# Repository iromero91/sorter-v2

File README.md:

# Sorter V2
## A LEGO® Sorting Machine

[More details](https://basically.website/sorter-v2)

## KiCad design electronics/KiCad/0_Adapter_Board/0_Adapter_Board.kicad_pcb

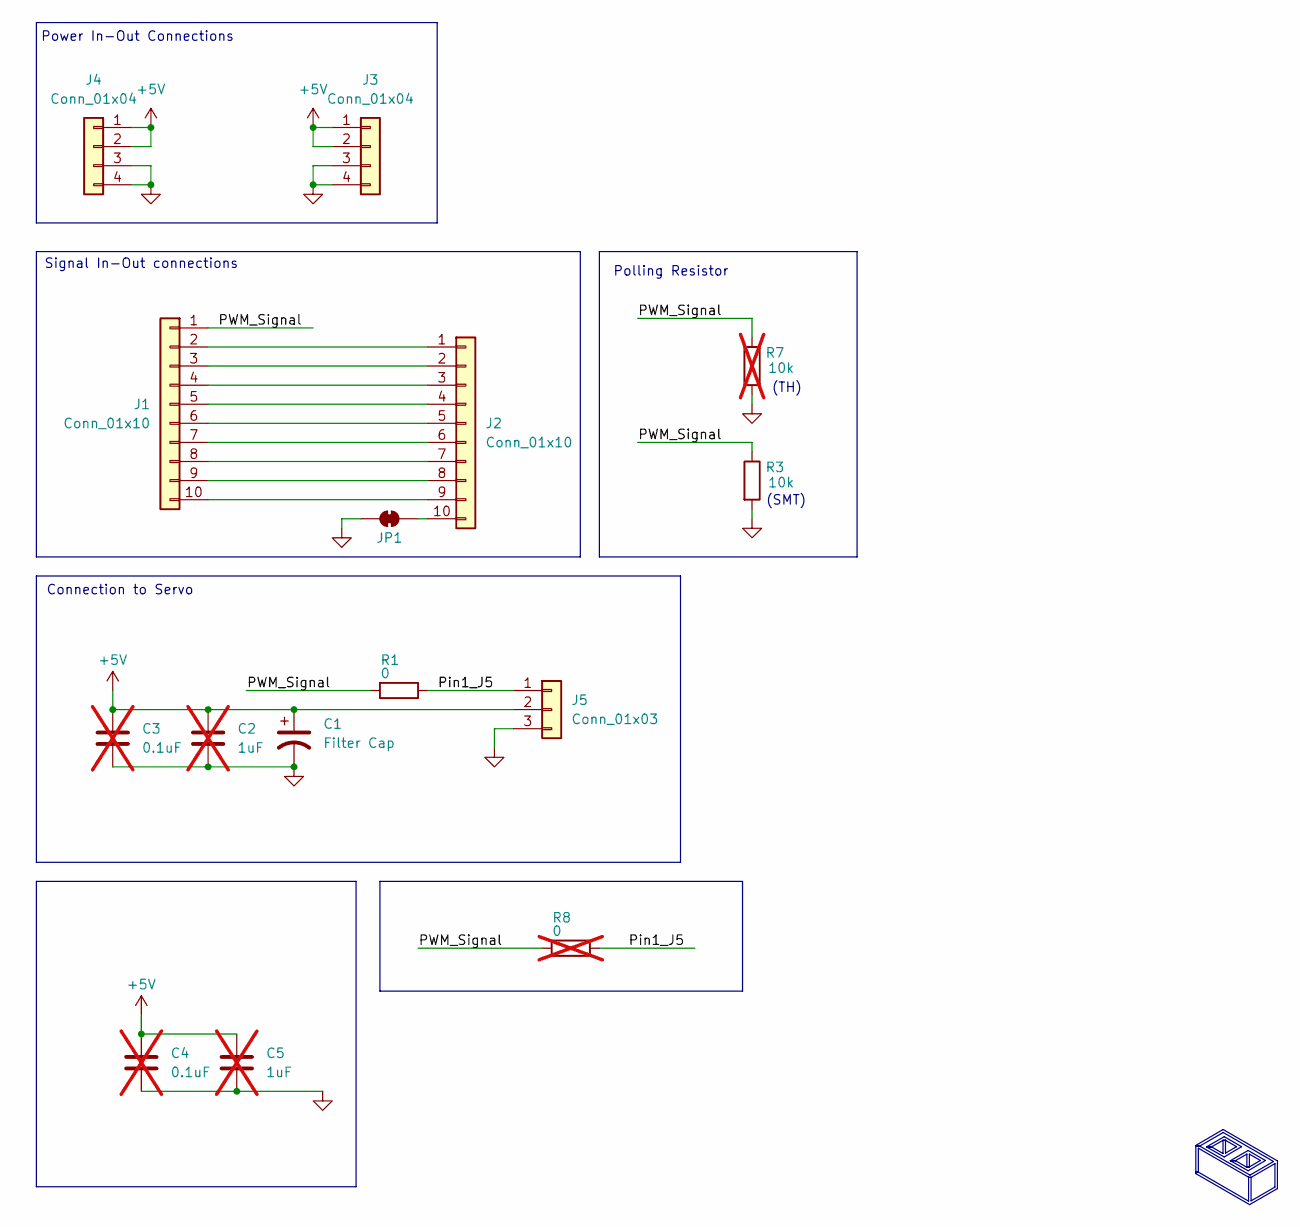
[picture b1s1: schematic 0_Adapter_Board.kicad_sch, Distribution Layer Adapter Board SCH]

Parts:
C1: Filter Cap; CP_Radial_D8.0mm_P2.50mm
C2: 1uF; C_0805_2012Metric_Pad1.18x1.45mm_HandSolder; not fitted
C3: 0.1uF; C_0805_2012Metric_Pad1.18x1.45mm_HandSolder; not fitted
C4: 0.1uF; C_Disc_D7.5mm_W2.5mm_P5.00mm; not fitted
C5: 1uF; C_Disc_D7.5mm_W2.5mm_P5.00mm; not fitted
J1, J2: Conn_01x10; JST_XA_B10B-XASK-1-A_1x10_P2.50mm_Vertical
J3, J4: Conn_01x04; JST_XA_B04B-XASK-1-A_1x04_P2.50mm_Vertical
J5: Conn_01x03; PinHeader_1x03_P2.54mm_Horizontal
JP1: SolderJumper_2_Bridged; SolderJumper-2_P1.3mm_Open_TrianglePad1.0x1.5mm
R1: 0; R_0805_2012Metric_Pad1.20x1.40mm_HandSolder
R3: 10k; R_0805_2012Metric_Pad1.20x1.40mm_HandSolder
R7: 10k; R_Axial_DIN0207_L6.3mm_D2.5mm_P10.16mm_Horizontal; not fitted
R8: 0; R_Axial_DIN0207_L6.3mm_D2.5mm_P10.16mm_Horizontal; not fitted

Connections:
+5V: C1.1, C2.1, C3.1, C4.1, C5.1, J3.1, J3.2, J4.1, J4.2, J5.2
/PWM_Signal: J1.1, R1.2, R3.1, R7.1, R8.2
/Pin1_J5: J5.1, R1.1, R8.1
GND: C1.2, C2.2, C3.2, C4.2, C5.2, J3.3, J3.4, J4.3, J4.4, J5.3, JP1.2 (B), R3.2, R7.2
unnamed: J1.2, J2.1
unnamed: J1.3, J2.2
unnamed: J1.4, J2.3
unnamed: J1.5, J2.4
unnamed: J1.6, J2.5
unnamed: J1.7, J2.6
unnamed: J1.8, J2.7
unnamed: J1.9, J2.8
unnamed: J1.10, J2.9
unnamed: J2.10, JP1.1 (A)

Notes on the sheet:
(SMT)
(TH)
Power In-Out Connections
Signal In-Out connections
Polling Resistor
Connection to Servo

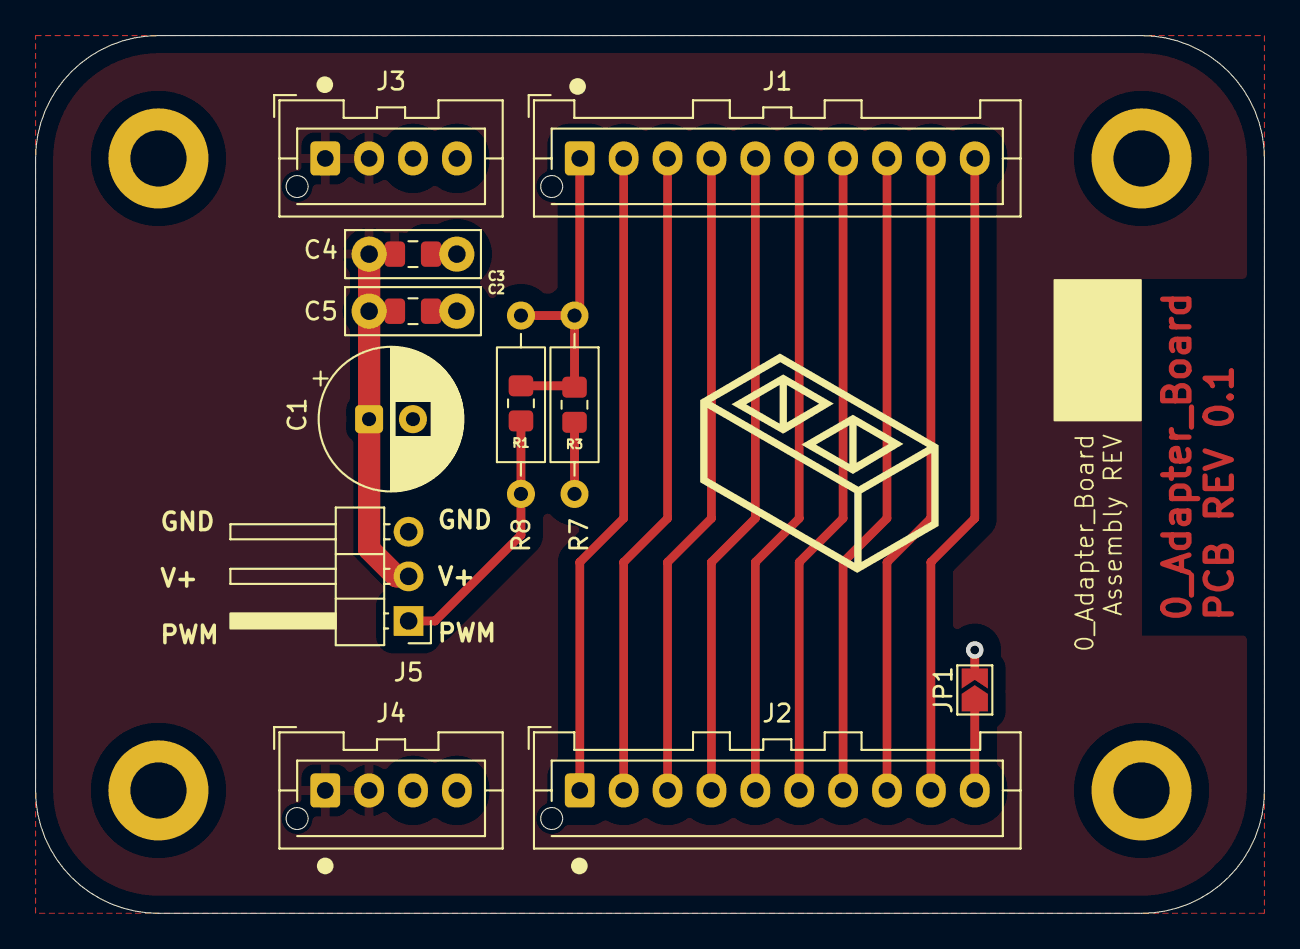
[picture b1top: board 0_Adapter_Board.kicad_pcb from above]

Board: 2 copper layers, 70.0 x 50.0 mm, 19 parts (0 on the bottom side), 14 nets.

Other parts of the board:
M1, M1#2, M1#3, M1#4: MountingHole_3.2mm_M3_ISO7380_Pad

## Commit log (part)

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2025-11-22 init readme folders and licenses
2025-11-23 ruff
2025-12-24 Added First version of the layer PCB
    Added layer stack PCBA for initial orders. Not clean in git. Files need identified that need uploaded. This is down and dirty for now.
2025-12-27 Added layer stack harness and directories
    Updated directories and added 4 and 10 wire harness for layer stack
2026-01-01 fix: rename folder
2026-01-07 import socket event types. heartbeat
2026-01-07 format
2026-01-10 wip firmware
2026-01-15 subsystem state machines
2026-01-21 dont crash when lose connection to web socket
2026-01-21 second mcu
2026-01-21 rudimentary classification state machine
2026-01-22 rotate chute, device discovery
2026-01-22 better chute angle calculation
2026-01-22 diff speeds per stepper. slightly more accurate angle calc
2026-01-22 re layout the ui, send KnownObjects to frontend
2026-01-23 change bl category lookup. param change
2026-01-23 feeder state machine
2026-01-23 show briclink stock photo in recent pieces
2026-01-23 pieces can have not found or unknown state
2026-01-23 runtime variables notion
2026-01-23 correctly working 3 channel state machine
2026-01-24 record raw video clips
2026-01-27 write full res frames. param changes
2026-01-27 requirements for cloud
2026-01-29 fix tag tracking
2026-01-30 functioning c-channel feeder
2026-02-07 example .env
2026-02-07 more accurate paths for example env
2026-02-07 update upload so can run from client dir
2026-02-07 rename arduino.ino to feeder.ino for compile cli
2026-02-07 add models via lfs
2026-02-07 track parts with categories data json
2026-02-07 add parts with categories json data via lfs
2026-02-08 Removed some testing code and expanded the demo to 4 motors.
2026-02-08 Finish initial communication implementation with test python module
2026-02-08 Add prototype communications code
2026-02-08 Tune the torture test
2026-02-09 acceleration
2026-02-09 run_id. put machine id on the global config
2026-02-10 just make this 8000
2026-02-10 New command dispatch strategy, more commands, correct some bugs.
2026-02-10 add python-dotenv + format
2026-02-10 webcam discovery helper script
2026-02-10 setup and run tutorial
2026-02-10 remove simple term menu because not supported on windows
2026-02-10 use dot env from the calibrate scripts
2026-02-11 dump logs to remote if telemetry
2026-02-12 Refactor command codes: remove enum definition
2026-02-12 rm unused param
2026-02-14 Fix memory alignment issues
2026-02-14 Fix incorrect command definitions
2026-02-15 Add README, remove old python test module (use the new driver instead)
2026-02-15 Add I2C detection in PCA9685 constructor to prevent initialization if device is not present
2026-02-15 Hook into the main code in a way that compiles (untested)
2026-02-16 bin layout customizable through json
2026-02-16 correct new gear ratio, home from chute calibrate, slower speed for chute motro
2026-02-17 auto discover arduino
2026-02-17 remove bin layout notion from ui and data pipeline
2026-02-17 type errors fix
2026-02-18 only rotate +180 deg and -180 from zero, which is on a pillar
2026-02-19 Fix pinouts, allow for multiple en pins
2026-02-19 Add custom build options for SKR Pico hardware support in README
2026-02-19 bright colors for aruco tags
2026-02-19 camera setup script
2026-02-19 just discover by index. opencv and ffmpeg get different camera indexes and so looking up index by name is unreliable
2026-02-20 Partial refactoring using copilot
2026-02-20 Initial plan
2026-02-20 Add root project files, licenses and contribution guidelines
2026-02-20 Split large initial commit into logical chunks
2026-02-21 Refactor Coordinator and SorterController to use SorterHardware, removing IRLInterface dependencies (PARTIAL WIP)
2026-02-21 Improve TMC UART reliability
    - Fix init order: call uart_init() before uart_set_format() so format
    settings are not overwritten
    - Increase read timeout from 120 to 250 bit periods to ensure full
    TMC2209 response is captured at all baud rates
    - Clear RX FIFO after setup to discard garbage from initialization
2026-02-21 Add fan pins, UART addresses, and fix CMake define for SKR Pico
    - Add FAN0 (GPIO17), FAN1 (GPIO18), FAN2 (GPIO20) to digital outputs
    - Add configurable TMC_UART_ADDRESSES[] array to both board configs so
    UART slave addresses can vary per board
    - Fix CMake preprocessor define: HW_SKR_PICO -> HARDWARE_SKR_PICO
2026-02-21 Fix some typing issues
2026-02-21 Implement ServoMotor class with control methods
